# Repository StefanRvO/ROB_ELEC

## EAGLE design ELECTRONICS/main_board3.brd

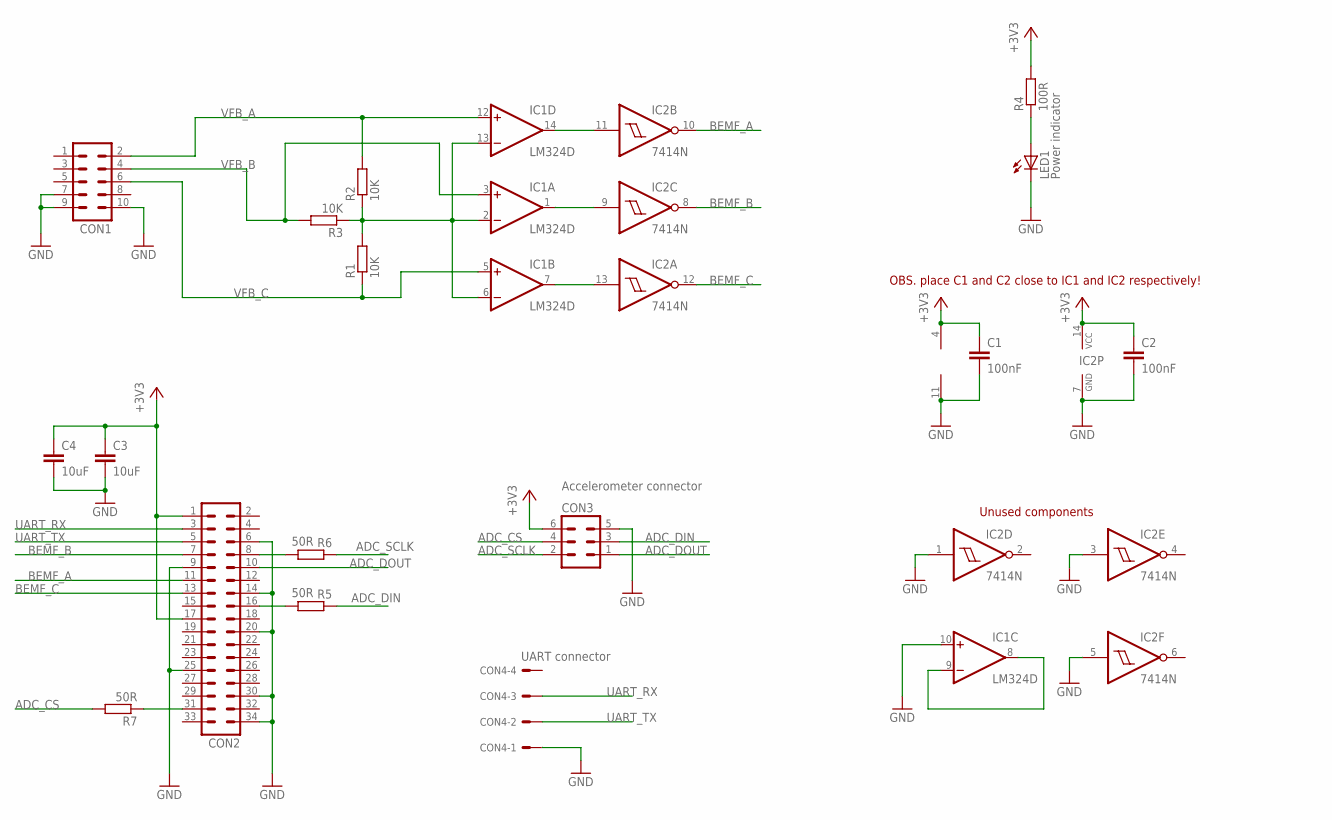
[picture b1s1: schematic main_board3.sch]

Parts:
C1, C2: 100nF; C0805K
C3, C4: 10uF; C1206K
CON1: MA05-2
CON2: MA17-2
CON3: Accelerometer connector; ML6
CON4: UART connector; 6410-04
IC1: LM324D; SO14
IC2: 7414N; DIL14
LED1: Power indicator; CHIP-LED0805
R1, R2, R3: 10K; R0805
R4: 100R; R0805
R5, R6, R7: 50R; R0805

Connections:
+3V3: C1.1, C2.1, C3.1, C4.1, CON2.1, CON2.17, CON3.6, IC1.4 (V+), IC2.14 (VCC), R4.2
ADC_CS: CON3.4, R7.2
ADC_DIN: CON3.3, R5.2
ADC_DOUT: CON2.10, CON3.1
ADC_SCLK: CON3.2, R6.2
BEMF_A: CON2.11, IC2.10 (O)
BEMF_B: CON2.7, IC2.8 (O)
BEMF_C: CON2.13, IC2.12 (O)
GND: C1.2, C2.2, C3.2, C4.2, CON1.7, CON1.9, CON1.10, CON2.6, CON2.9, CON2.14, CON2.20, CON2.25, CON2.30, CON2.34, CON3.5, CON4.1, IC1.10 (+IN), IC1.11 (V-), IC2.1 (I), IC2.3 (I), IC2.5 (I), IC2.7 (GND), LED1.C
unnamed: IC1.14 (OUT), IC2.11 (I)
unnamed: IC1.1 (OUT), IC2.9 (I)
unnamed: IC1.7 (OUT), IC2.13 (I)
unnamed: IC1.2 (-IN), IC1.6 (-IN), IC1.13 (-IN), R1.2, R2.1, R3.1
unnamed: CON2.8, R6.1
unnamed: CON2.16, R5.1
unnamed: LED1.A, R4.1
unnamed: CON2.31, R7.1
unnamed: IC1.8 (OUT), IC1.9 (-IN)
UART_RX: CON2.3, CON4.3
UART_TX: CON2.5, CON4.2
VFB_A: CON1.2, IC1.12 (+IN), R2.2
VFB_B: CON1.4, IC1.3 (+IN), R3.2
VFB_C: CON1.6, IC1.5 (+IN), R1.1

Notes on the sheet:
OBS. place C1 and C2 close to IC1 and IC2 respectively!
Unused components

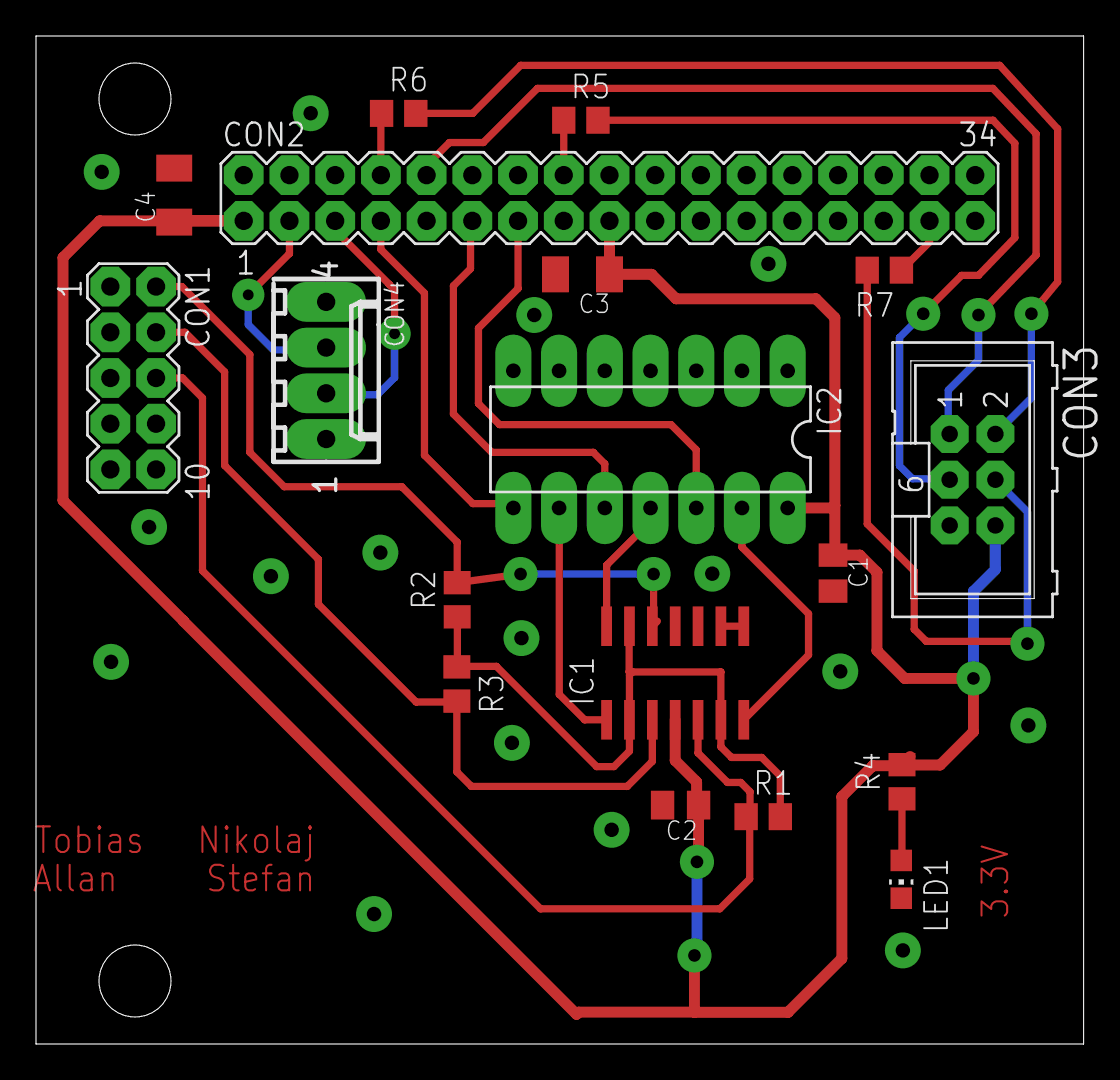
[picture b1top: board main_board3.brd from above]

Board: 2 copper layers, 58.2 x 56.0 mm, 18 parts (0 on the bottom side), 23 nets.

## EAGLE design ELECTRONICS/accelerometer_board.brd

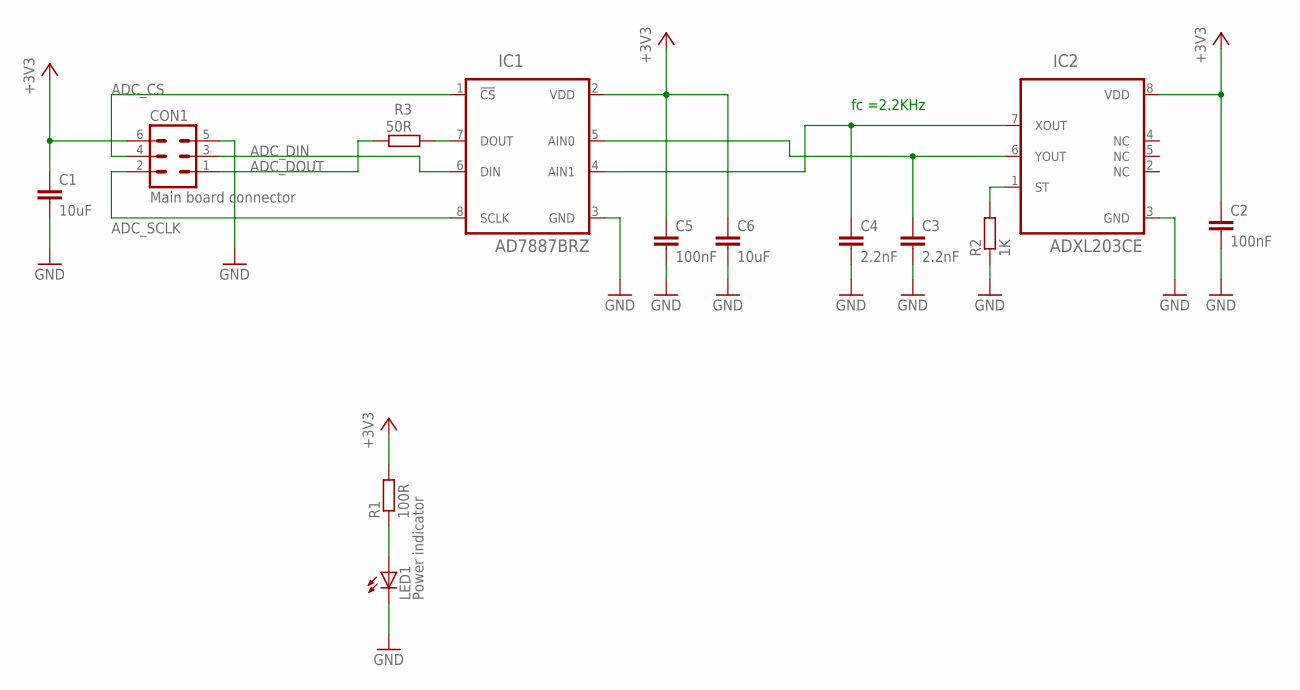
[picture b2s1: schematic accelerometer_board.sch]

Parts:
C1, C6: 10uF; C1206K
C2, C5: 100nF; C0805K
C3, C4: 2.2nF; C0805K
CON1: Main board connector; ML6
IC1: AD7887BRZ; SO08
IC2: ADXL203CE; LCC127P500X500X220-8N
LED1: Power indicator; CHIP-LED0805
R1: 100R; R0805
R2: 1K; R0805
R3: 50R; R0805

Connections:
+3V3: C1.1, C2.1, C5.1, C6.1, CON1.6, IC1.2 (VDD), IC2.8 (VDD), R1.2
ADC_CS: CON1.4, IC1.1 (!CS)
ADC_DIN: CON1.3, IC1.6 (DIN)
ADC_DOUT: CON1.1, R3.2
ADC_SCLK: CON1.2, IC1.8 (SCLK)
GND: C1.2, C2.2, C3.2, C4.2, C5.2, C6.2, CON1.5, IC1.3 (GND), IC2.3 (GND), LED1.C, R2.1
unnamed: C4.1, IC1.4 (AIN1), IC2.7 (XOUT)
unnamed: LED1.A, R1.1
unnamed: IC2.1 (ST), R2.2
unnamed: IC1.7 (DOUT), R3.1
unnamed: C3.1, IC1.5 (AIN0), IC2.6 (YOUT)

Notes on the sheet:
fc =2.2KHz

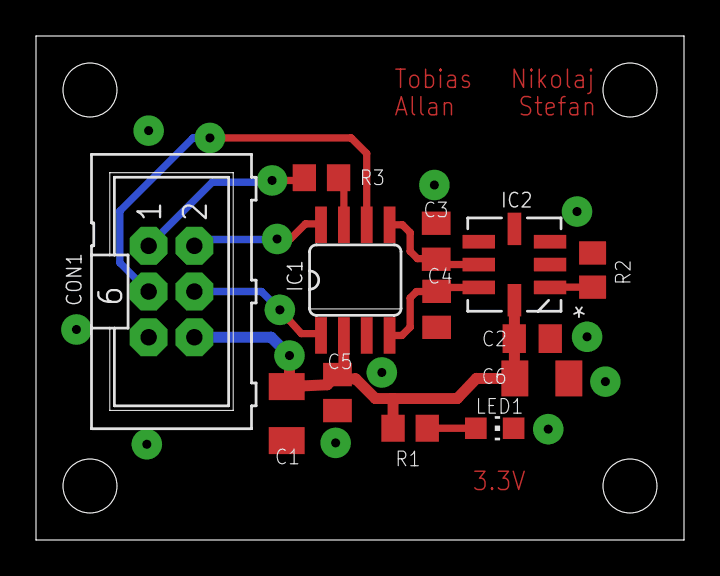
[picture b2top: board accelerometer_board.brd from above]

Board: 2 copper layers, 36.0 x 28.0 mm, 13 parts (0 on the bottom side), 11 nets.

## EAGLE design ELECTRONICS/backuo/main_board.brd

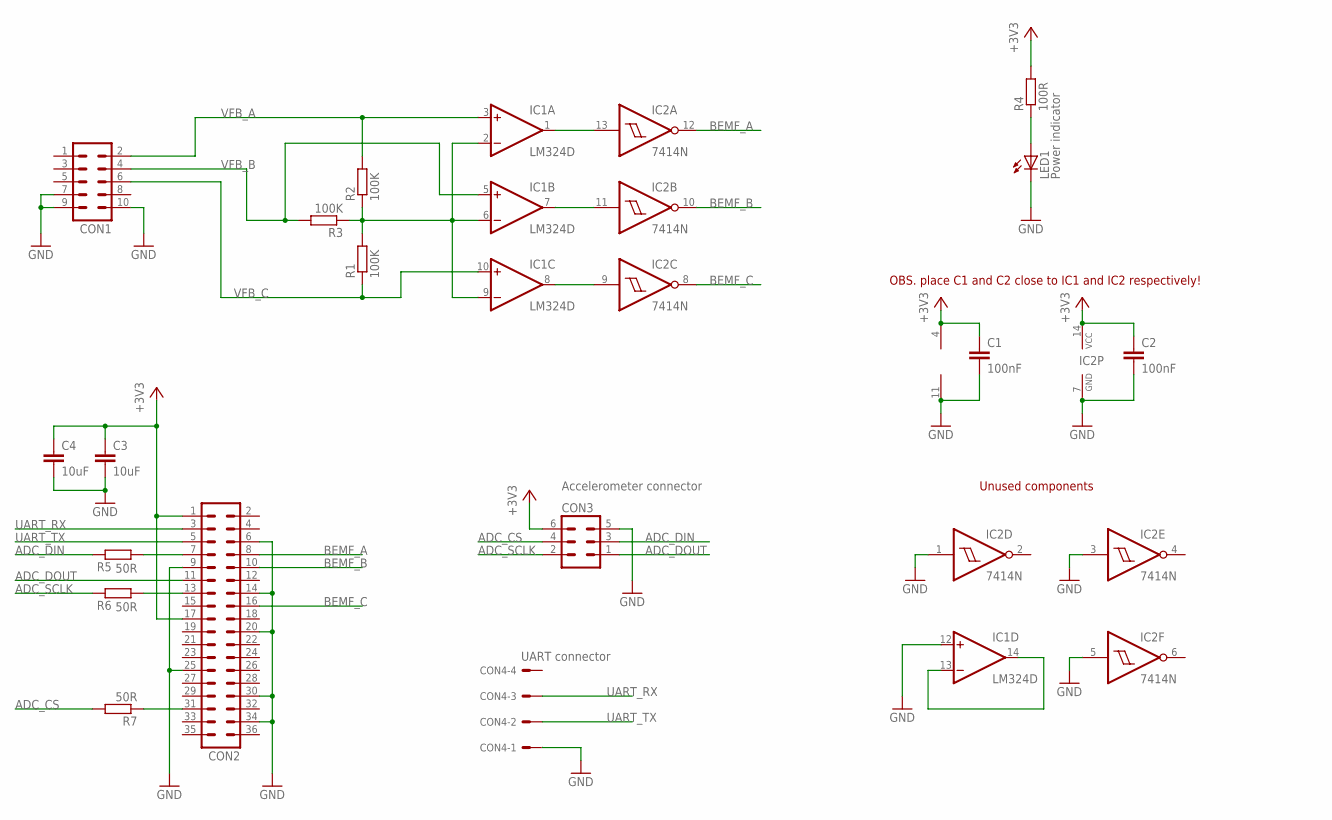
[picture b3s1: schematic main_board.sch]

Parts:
C1, C2: 100nF; C0805K
C3, C4: 10uF; C1206K
CON1: MA05-2
CON2: MA18-2
CON3: Accelerometer connector; ML6
CON4: UART connector; 6410-04
IC1: LM324D; SO14
IC2: 7414N; DIL14
LED1: Power indicator; CHIP-LED0805
R1, R2, R3: 100K; R0805
R4: 100R; R0805
R5, R6, R7: 50R; R0805

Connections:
+3V3: C1.1, C2.1, C3.1, C4.1, CON2.1, CON2.17, CON3.6, IC1.4 (V+), IC2.14 (VCC), R4.2
ADC_CS: CON3.4, R7.2
ADC_DIN: CON3.3, R5.2
ADC_DOUT: CON2.11, CON3.1
ADC_SCLK: CON3.2, R6.2
BEMF_A: CON2.8, IC2.12 (O)
BEMF_B: CON2.10, IC2.10 (O)
BEMF_C: CON2.16, IC2.8 (O)
GND: C1.2, C2.2, C3.2, C4.2, CON1.7, CON1.9, CON1.10, CON2.6, CON2.9, CON2.14, CON2.20, CON2.25, CON2.30, CON2.34, CON3.5, CON4.1, IC1.11 (V-), IC1.12 (+IN), IC2.1 (I), IC2.3 (I), IC2.5 (I), IC2.7 (GND), LED1.C
unnamed: IC1.1 (OUT), IC2.13 (I)
unnamed: IC1.7 (OUT), IC2.11 (I)
unnamed: IC1.8 (OUT), IC2.9 (I)
unnamed: IC1.2 (-IN), IC1.6 (-IN), IC1.9 (-IN), R1.2, R2.1, R3.1
unnamed: CON2.7, R5.1
unnamed: CON2.13, R6.1
unnamed: LED1.A, R4.1
unnamed: CON2.31, R7.1
unnamed: IC1.13 (-IN), IC1.14 (OUT)
UART_RX: CON2.3, CON4.3
UART_TX: CON2.5, CON4.2
VFB_A: CON1.2, IC1.3 (+IN), R2.2
VFB_B: CON1.4, IC1.5 (+IN), R3.2
VFB_C: CON1.6, IC1.10 (+IN), R1.1

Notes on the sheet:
OBS. place C1 and C2 close to IC1 and IC2 respectively!
Unused components

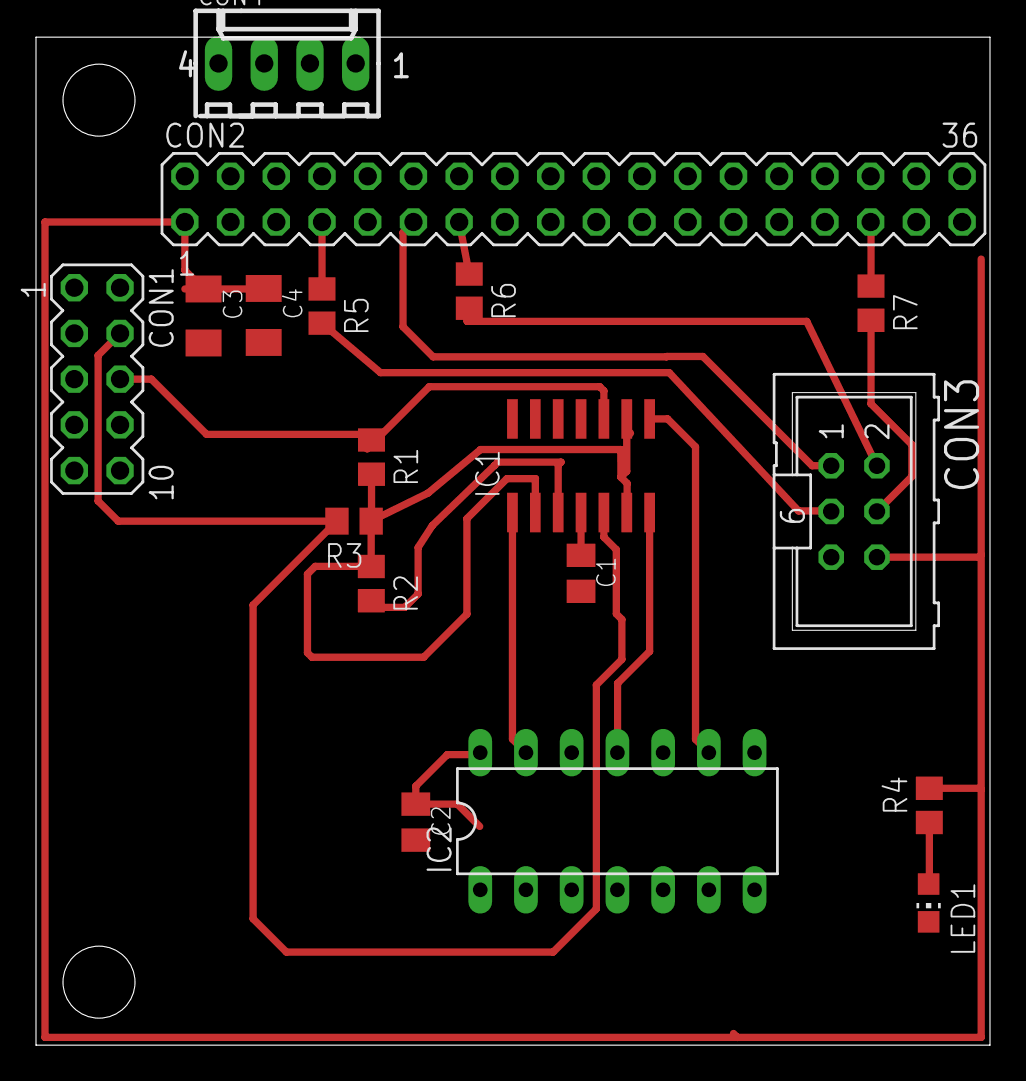
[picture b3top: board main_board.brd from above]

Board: 2 copper layers, 53.0 x 56.0 mm, 18 parts (0 on the bottom side), 23 nets.

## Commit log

2016-11-15 Working PWM on H-bridge controlled by the encoder.
2016-11-16 Added gitignore
2016-11-16 Added unity link stuff.
2016-11-22 added BLDC controller.
2016-11-23 Fixed stuff..
2016-11-23 Stuff....
2016-11-24 saved state.
2016-11-24 Added a lot of BLDC control stuff.
2016-12-07 Fixed some stuff.. or something..
2016-12-07 Tried to fix stuff.
2016-12-07 Added electronics folder.
2016-12-07 Electronics schematic is added
2016-12-07 Electronics schematics is added
2016-12-07 Accelerometer and ADC is created and the circuit design is started
2016-12-07 Running average seems to be working ok. PID implemented but not tested, probably need some fixes.
2016-12-08 PID seems to be working, but needs changes. LUT usage is huge...
2016-12-08 Somewhat fixed PID and running avg to use less parts.
2016-12-08 vivado vomit.
2016-12-16 Schematics are finish
2016-12-17 Some edits.
2016-12-17 Added board files.
2016-12-17 A lot of FPGA edits.
2016-12-17 Accelerometer PCB is finish! :)
2016-12-19 Changes and stuff.
2016-12-19 Main board is almost finished
2016-12-20 PCB is finished for both boards
2016-12-21 Final PCB
2016-12-21 Deleted back.
